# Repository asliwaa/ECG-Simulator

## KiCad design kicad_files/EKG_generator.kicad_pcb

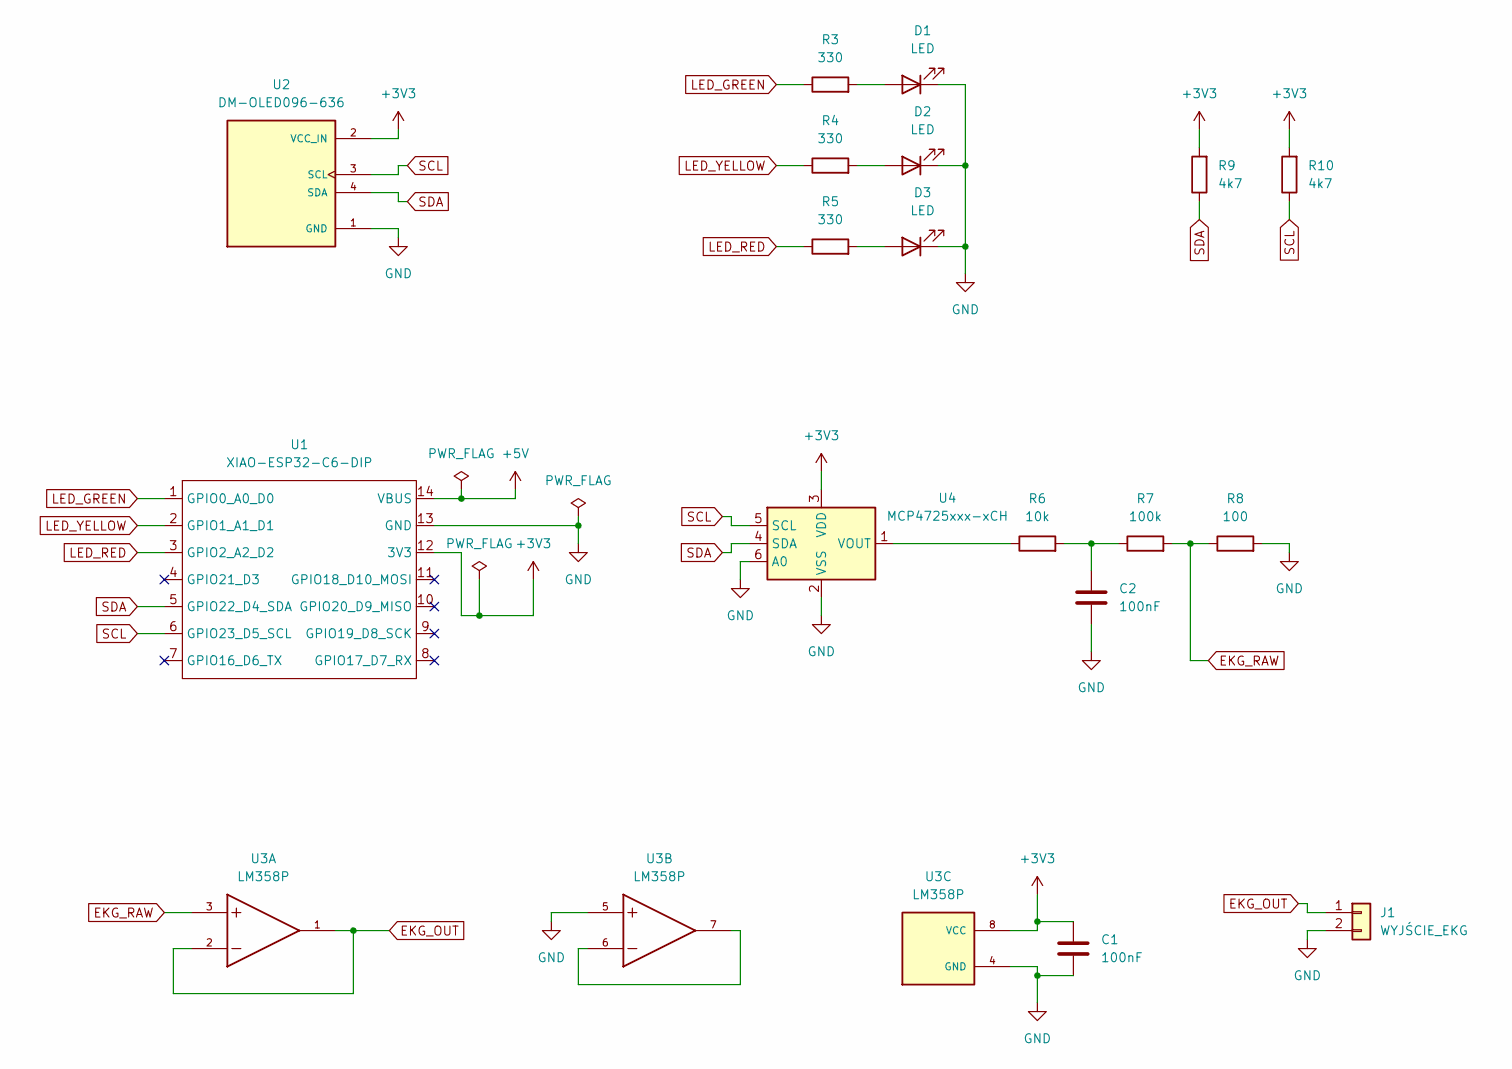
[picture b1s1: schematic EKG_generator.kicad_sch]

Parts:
C1, C2: 100nF; C_Disc_D5.0mm_W2.5mm_P5.00mm
D1, D2, D3: LED; LED_D5.0mm
J1: WYJŚCIE_EKG; PinHeader_1x02_P2.54mm_Vertical
R3, R4, R5: 330; R_Axial_DIN0207_L6.3mm_D2.5mm_P10.16mm_Horizontal
R6: 10k; R_Axial_DIN0207_L6.3mm_D2.5mm_P10.16mm_Horizontal
R7: 100k; R_Axial_DIN0207_L6.3mm_D2.5mm_P10.16mm_Horizontal
R8: 100; R_Axial_DIN0207_L6.3mm_D2.5mm_P10.16mm_Horizontal
R9, R10: 4k7; R_Axial_DIN0207_L6.3mm_D2.5mm_P10.16mm_Horizontal
U1: XIAO-ESP32-C6-DIP
U2: DM-OLED096-636; MODULE_DM-OLED096-636; PARTREV 2018-09-10
U3: LM358P; DIP-8_W7.62mm; PARTREV FEBRUARY 2021
U4: MCP4725xxx-xCH; SOT-23-6

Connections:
+3V3: C1.1, R9.2, R10.2, U1.12 (3V3), U2.2 (VCC_IN), U3.8 (VCC), U4.3 (VDD)
+5V: U1.14 (VBUS)
EKG_OUT: J1.1, U3.1, U3.2
EKG_RAW: R7.2, R8.1, U3.3
GND: C1.2, C2.2, D1.1 (K), D2.1 (K), D3.1 (K), J1.2, R8.2, U1.13 (GND), U2.1 (GND), U3.4 (GND), U3.5, U4.2 (VSS), U4.6 (A0)
LED_GREEN: R3.1, U1.1 (GPIO0_A0_D0)
LED_RED: R5.1, U1.3 (GPIO2_A2_D2)
LED_YELLOW: R4.1, U1.2 (GPIO1_A1_D1)
unnamed: C2.1, R6.2, R7.1
unnamed: D1.2 (A), R3.2
unnamed: D2.2 (A), R4.2
unnamed: D3.2 (A), R5.2
unnamed: U3.6, U3.7
unnamed: R6.1, U4.1 (VOUT)
SCL: R10.1, U1.6 (GPIO23_D5_SCL), U2.3 (SCL), U4.5 (SCL)
SDA: R9.1, U1.5 (GPIO22_D4_SDA), U2.4 (SDA), U4.4 (SDA)

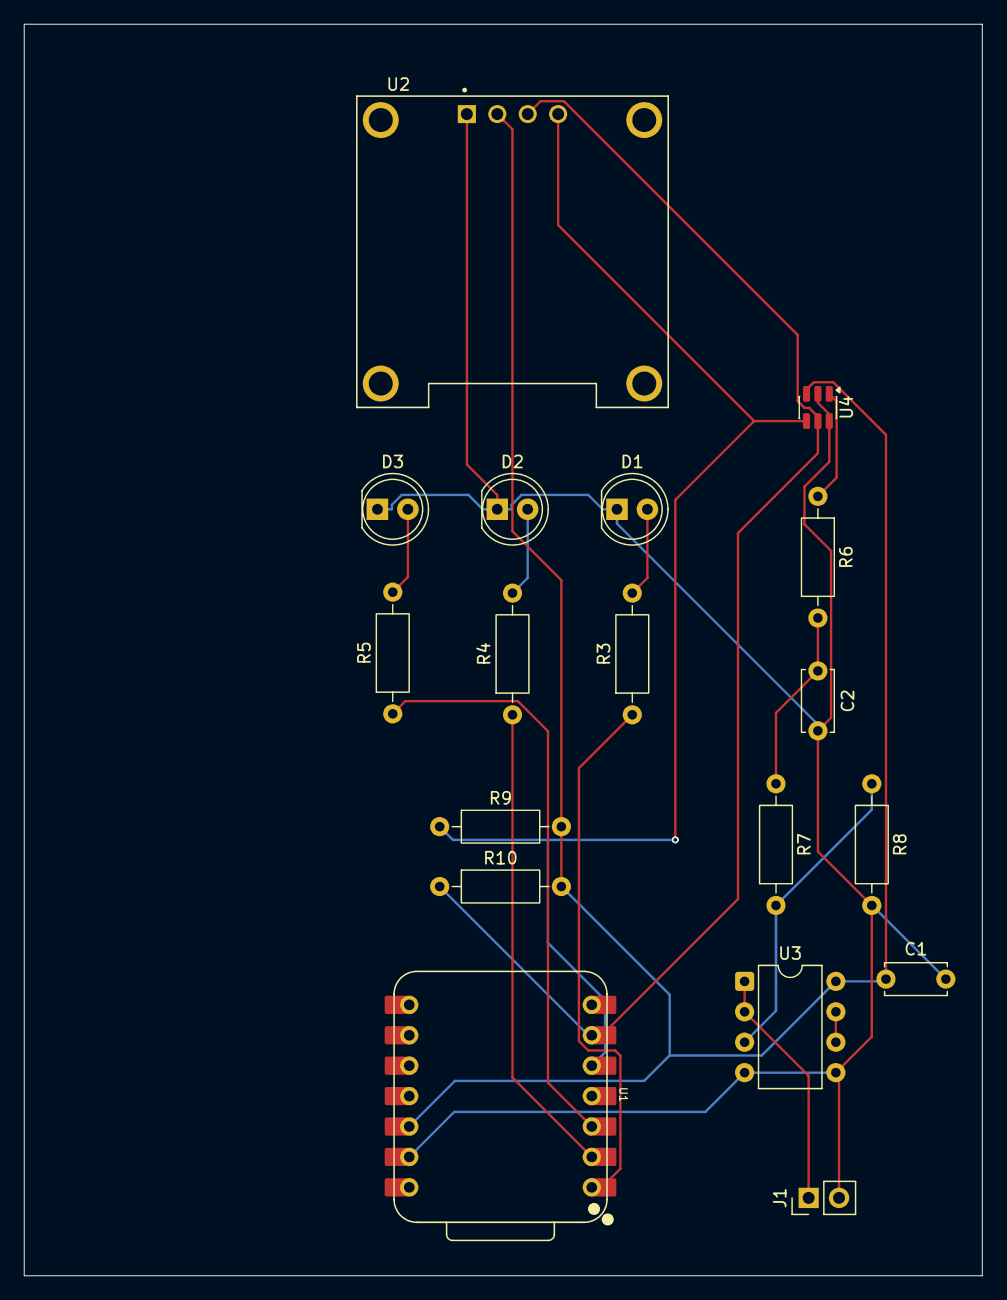
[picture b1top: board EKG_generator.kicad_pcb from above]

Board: 2 copper layers, 80.0 x 104.5 mm, 18 parts (0 on the bottom side), 15 nets.

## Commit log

2026-04-09 'init'
2026-05-09 Complete routing on PCB
2026-06-16 Add .gitignore
2026-06-16 chore: add code logic file
2026-06-22 Code done
2026-06-25 Final
